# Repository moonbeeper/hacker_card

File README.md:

# Moon's Hacker Card

Its my own hacker pcb card! It has the typical stuff a NFC chip and art made by me and birb.

sadly it was done in speedrun mode lol. I will try to make the readme better in the future!!!

For future info, I've used the hack club's [hack card](https://jams.hackclub.com/jam/hacker-card) guide for making this card!

## Images

> The first image is the front and the second one is the back.

## BOM

> Shipping costs might be higher!

> NOTE: It's a copy of the bom.csv file from the production folder.

| Designator           | Footprint                                      | Quantity | Value               | LCSC Part # | Price   |
|----------------------|------------------------------------------------|----------|----------------------|-------------|---------|
| 220nF Capacitor      | 0603                                           | 1        | 220nF               |             |         |
| LED Yellow-Green     | 0805                                           | 1        | LED                 |             |         |
| NFC Antenna - Wire   | 25X48MM_NFC                                    | 1        | 25X48MM_NFC_ANTENNA |             |         |
| 47 Resistor          | 0603                                           | 1        | 47                  |             |         |
| NFC Chip             | XQFN-8_L1.6-W1.6-P0.50-BL_NT3H2111W0FHKH       | 1        | NT3H2111W0FHKH      | C710403     |         |
| **PCBs**             |                                                | 5        |                      |             | **$2** |
| **PCBA Total**       |                                                | 2        |                      |             | **$15.12** |
| **~Shipping**        |                                                |          |                      |             | **$15.00** |
| **Total**            |                                                |          |                      |             | **$32.12** |

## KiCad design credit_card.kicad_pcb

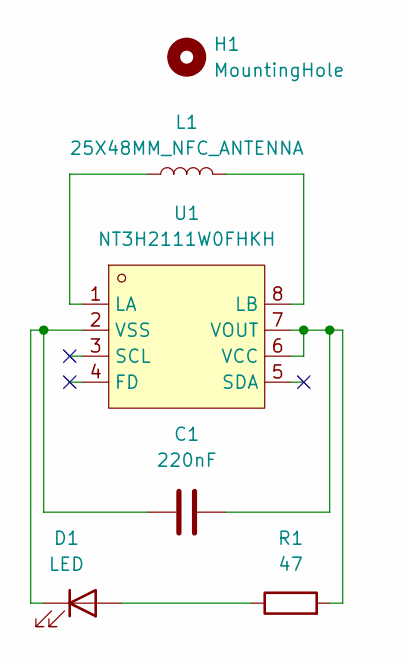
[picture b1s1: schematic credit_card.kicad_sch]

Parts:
C1: 220nF; C_0603_1608Metric
D1: LED; LED_0805_2012Metric
H1: MountingHole; MountingHole_5.3mm_M5
L1: 25X48MM_NFC_ANTENNA; 25X48MM_NFC
R1: 47; R_0603_1608Metric
U1: NT3H2111W0FHKH; XQFN-8_L1.6-W1.6-P0.50-BL_NT3H2111W0FHKH; LCSC Part C710403

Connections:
unnamed: D1.2 (A), R1.1
unnamed: C1.1, D1.1 (K), U1.2 (VSS)
unnamed: L1.1, U1.1 (LA)
unnamed: L1.2, U1.8 (LB)
unnamed: C1.2, R1.2, U1.6 (VCC), U1.7 (VOUT)

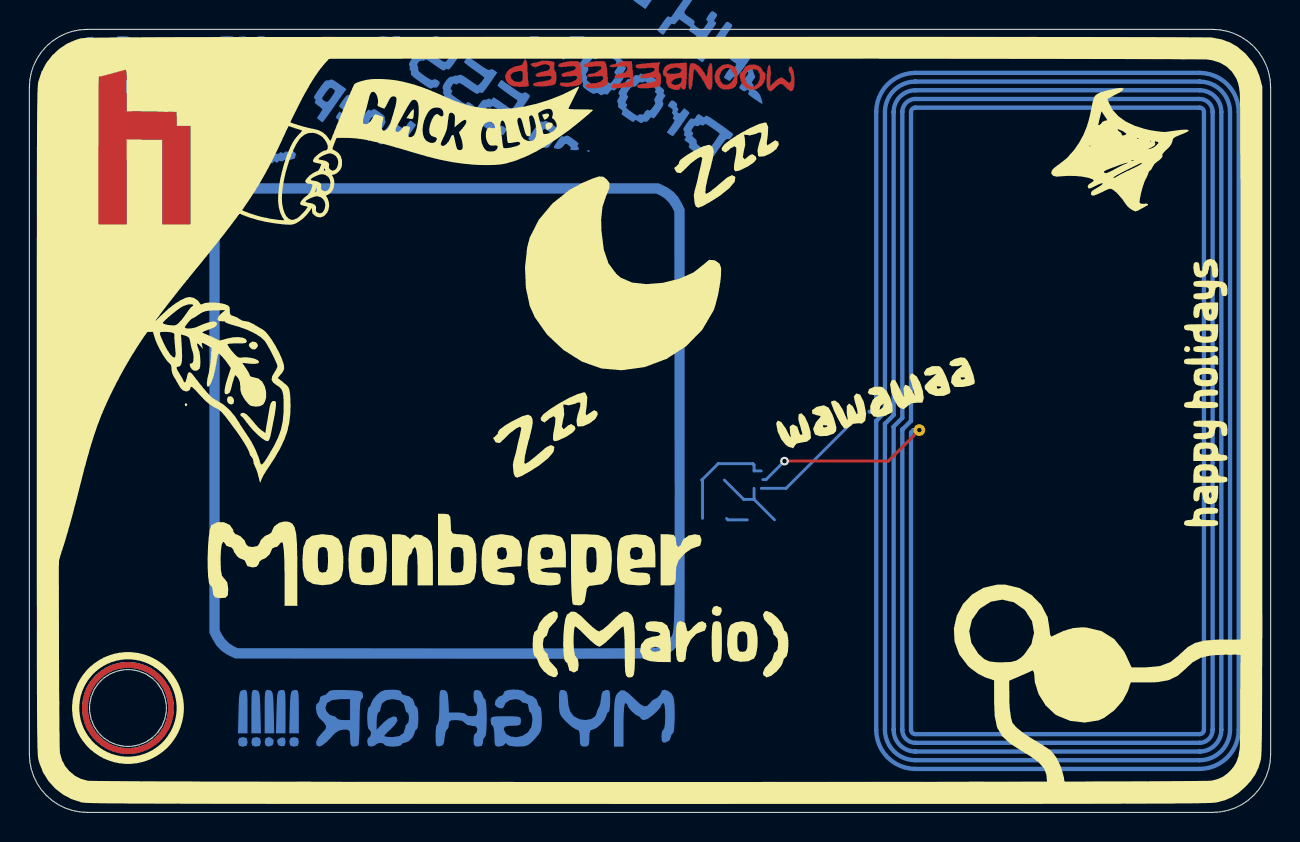
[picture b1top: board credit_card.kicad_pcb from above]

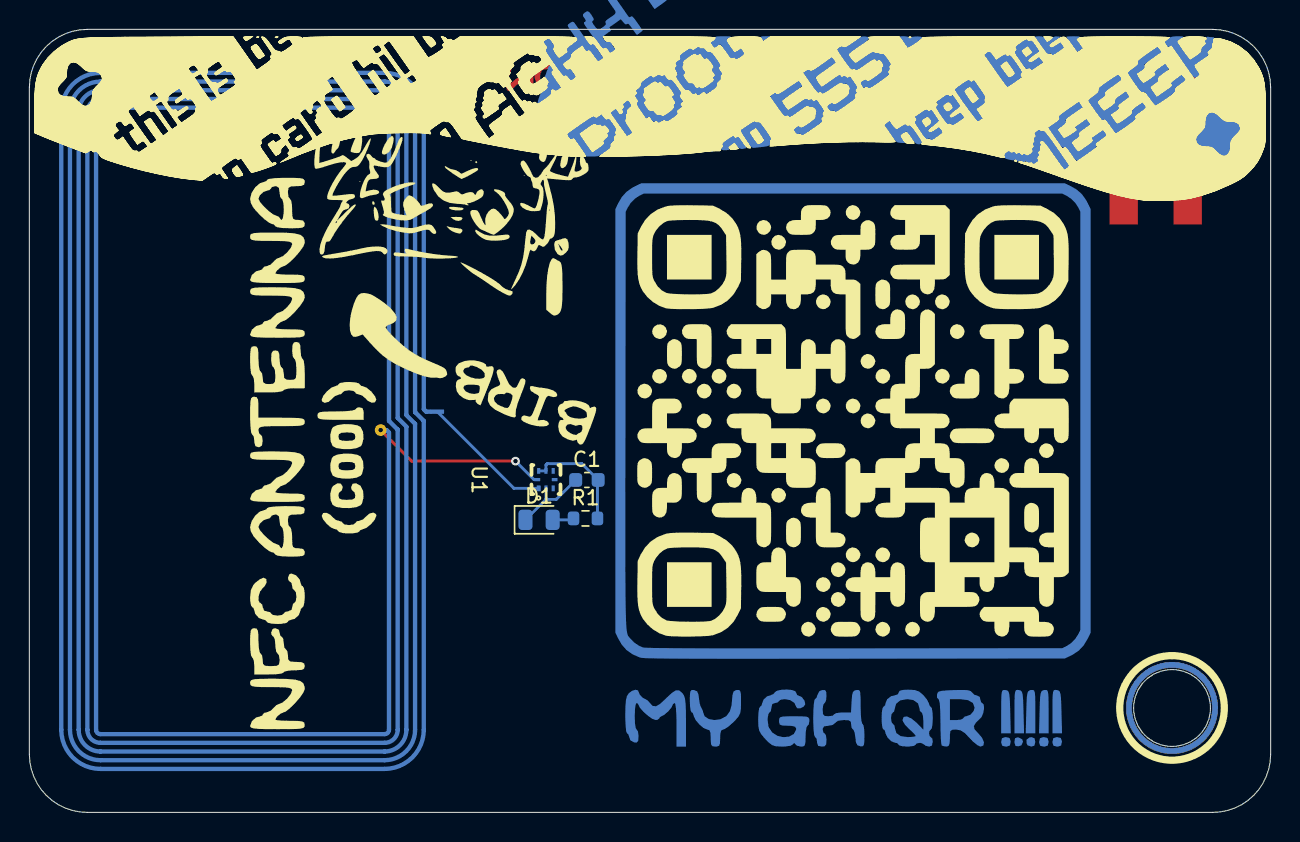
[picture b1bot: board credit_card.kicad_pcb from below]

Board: 2 copper layers, 85.6 x 54.0 mm, 6 parts (5 on the bottom side), 5 nets.

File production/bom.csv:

Designator,Footprint,Quantity,Value,LCSC Part #
C1,0603,1,220nF,
D1,0805,1,LED,
L1,25X48MM_NFC,1,25X48MM_NFC_ANTENNA,
R1,0603,1,47,
U1,XQFN-8_L1.6-W1.6-P0.50-BL_NT3H2111W0FHKH,1,NT3H2111W0FHKH,C710403

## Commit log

2025-08-01 push
2025-08-01 forgot
2025-08-01 didn't commit?
2025-08-01 fix nfc antenna issues
2025-08-01 fix center lines inside wrong layer
2025-08-01 remove REF in silkscreen
